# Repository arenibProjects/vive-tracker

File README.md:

# vive-tracker

This repository contains followings folders :
 - cad : 3d models of the beacons and the lighthouse (Solidworks 2016 format)
 - docs : datasheets, reports, ...
 - eda : BOM/Gerber files for PCBs
 - imgs : images for reports

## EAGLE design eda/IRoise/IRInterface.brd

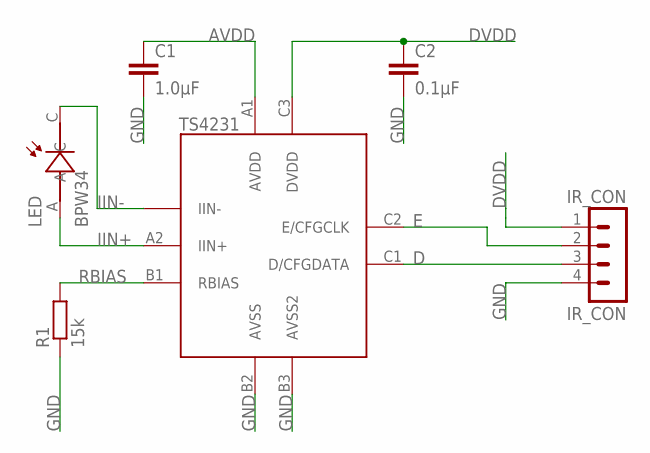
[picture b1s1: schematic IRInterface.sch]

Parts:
C1: 1.0µF; C0402
C2: 0.1µF; C0402
IR_CON: IR_CON; MA04-1
LED: BPW34; PHODET_BPW34
R1: 15k; R0402
TS4231: TS4231SMD-9; WLCSP-9

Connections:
AVDD: C1.1, TS4231.A1 (AVDD)
D: IR_CON.3, TS4231.C1 (D/CFGDATA)
DVDD: C2.1, IR_CON.1, TS4231.C3 (DVDD)
E: IR_CON.2, TS4231.C2 (E/CFGCLK)
GND: C1.2, C2.2, IR_CON.4, R1.1, TS4231.B2 (AVSS), TS4231.B3 (AVSS2)
IIN+: LED.A, TS4231.A2 (IIN+)
IIN-: LED.C, TS4231.A3 (IIN-)
RBIAS: R1.2, TS4231.B1 (RBIAS)

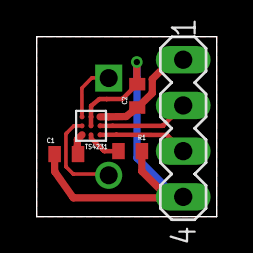
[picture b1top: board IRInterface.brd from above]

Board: 2 copper layers, 10.0 x 10.0 mm, 6 parts (1 on the bottom side), 8 nets.

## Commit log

2017-12-15 Begin latex report
2017-12-15 Add vive pulse simulator
2017-12-20 Add IRInterface eagle files
2017-12-20 Add TS231 orientation drawing
2017-12-20 Add .gitignore files
    Ignore PSoC Creator auto-generated files.
    Ignore *.zip files.
2017-12-20 Add ViveBeacon PSoC Creator project
2017-12-24 Add other .gitignore files
    .gitignore files for Eagle and LaTeX.
2017-12-27 Add .log files to .gitignore
2017-12-29 New architecture for VIVEDecoders using Datapath
    This new architecture is more ressource efficient in the PSoC. It uses 16 datapaths to compute the timing and the sync pulse length. It also decodes the sync pulse length. This architecture allows ot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
2018-01-22 VIVEDecoder architecture update with addition of XBEE and IMU communication peripherals
    This architecture is more resilient if there's an light occlusion when the sensor is in counting state. Pulse length decoding will be done in software because some datapath ressources were moved from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
    Adding UART peripheral for XBEE communication.
    Adding I2C Master peripheral for IMU communication.
2018-01-22 Add a kalman filter test Scilab script
2018-02-23 Create VIVE_Sensors module and Hardware design correction
    Create VIVE_Sensors module and and correction of hardware design after some tests.
2018-02-25 [BUGFIX] DMA
    Change DMA source adress.
2018-03-07 Change from CY8C5888AXQ-LP096 to CY8C5888AXI-LP096 in project settings.
2018-03-07 Change to SWD debugging mode in project settings.
2018-03-07 Extend heap size in project settings
    This will allow the use of (m|c|re)alloc() functions from stdlib.h.
2018-03-07 Add the planned firmware architecture for vive beacons v1.0
2018-03-07 Add TS4231_driver module
    This module is an portage of TS4231 Arduino Library from Triad Semiconductors (https://github.com/TriadSemi/TS4231) on the PSoC 5LP.
    This module allows us to :
    - Correctly configure the TS4231 chip.
    - Switch between SLEEP and WATCH mode dynamically to save power.
    This commit also provides a little code to test it.
2018-03-08 Hardware design correction for use with configured TS4231
2018-03-29 vive_sensors module completed
2018-03-29 Add header protection on TS4231_driver module
2018-03-29 Add Position_finder module
2018-03-29 Add XBee_commands module files
2018-03-29 Refactor main function
2018-03-29 Add configuration.h file
2018-03-29 Update project (X) file
2018-04-05 Extend heap size
    Extend heap size to 0x8000 (32kB) instead of 0x1000 (4kB).
2018-04-05 5th April 2018's commit
    This commit includes :
    - VIVEDecoder readable bit debugging
    - VIVE_sensors module debugging
    - Code reorganization
    - Add a time timer
2018-04-05 Commandify main.c for tests
2018-04-05 Reject more angles values
2018-04-05 Axis of AWESOME !
2018-04-08 VIVE_CLK synch with BUS_CLK
2018-04-08 Add maths library
2018-04-08 VIVE_sensors module correction
    - Forgot one DMA transfert.
    - Better voting system
2018-04-08 LEDs Positions done !
    With temporary LEDPOS command implemented.
2018-04-08 Add beacon configuration lines
2018-04-09 Remove debugging lines in Position_finder_find_position
2018-04-10 Add tracker led offset in configuration.h
2018-04-10 Switch to pointer for led_positions in find_position method
2018-04-10 Heading computation
2018-04-10 Don't forget to free before (re-)malloc
2018-04-10 lighthouse support v1 and iroise files
2018-04-11 iroise reiforced
2018-04-11 HEADING working
2018-04-11 iroise support and aesthetic update
    missing tabs
2018-04-11 iroise tabs
2018-04-11 iroise stl export
2018-04-12 Real values for tracker_led_offset
2018-04-15 update iroise top holder
2018-04-16 Create of USB_commands module
2018-04-17 Correction of NaN bugs and switch to a median filter instead of an average filter
2018-04-17 Update project files
2018-04-17 Correction after some IRInterface destruction
    "Correction of NaN bugs and switch to a median filter instead of an average filter" commit is also concerned.
2018-04-21 X and Y coordinates computation with median filter
2018-04-26 USB_commands commit 1
2018-04-26 USB_commands commit 2
2018-05-02 Add UART_commands_manager module
    Allows Teensy or any Arduino-like computer to communicate with the vive tracker without hosting an USB connection.
2018-05-02 Refactoring code
2018-05-02 [BUGFIX] Plugged an issue
    malloc() and free() : Well, it's always better together
2018-05-08 Modif' pour découpe laser
2018-05-23 Edit .gitignore for LaTeX files
2018-05-23 Changes ocurred during the French national robotic cup
2018-05-23 Reorganization of LaTeX files
2018-05-23 Edit .gitignore for LaTeX files - again
2018-05-23 [BUGFIX] LaTeX folders rename
2018-05-25 Introduction beginning
2018-05-25 Starting of overall view and electronic design
2018-07-15 Add comments to the code
    Hopefully, this will helps users (or future mainteners) of this system to understand what the firmware does.
2018-09-13 Update documentation
2018-09-13 Update code
